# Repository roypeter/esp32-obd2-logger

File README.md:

# ESP32 OBD2 CAN Logger

A DIY OBD2 data logger built with an ESP32. Reads live engine data over CAN bus, logs to CSV (SD card or internal flash), shows live values on a small OLED display, and serves a real-time web dashboard over WiFi.

> **Note:** Only tested on a **2020 Tata Nexon 1.2L Turbo Petrol (6-speed manual)**. Should work on any car with standard OBD2 over CAN (ISO 15765-4, 500 kbps).

## Using AI to review your driving data

Download the CSV from the WiFi dashboard and upload it to an AI model like **Claude** or **Gemini Pro**. You can ask questions like:

- "How is the turbo performance?"
- "Review if all sensors are working correctly and flag any issues"
- "Is the fuel trim normal or is the engine running rich/lean?"
- "Any signs of engine problems based on this data?"

The AI can analyze thousands of rows of sensor data in seconds and give you a plain-English health report of your car.

Here's an example report generated from a real driving session:

## What it does

- Reads **30+ OBD2 PIDs**: RPM, speed, coolant temp, oil temp, MAP, IAT, engine load, timing advance, throttle, accelerator pedal, fuel trims, O2 sensors, catalyst temp, fuel rate, voltage, and more
- **Logs to CSV** at ~4 Hz with automatic session numbering — SD card preferred, falls back to ESP32 internal flash (LittleFS) if no SD card is present
- **OLED display** (optional) — rotates between live data, running averages, and session stats (max boost, trip distance, fuel economy)
- **WiFi dashboard** — connect your phone to see live gauges, download CSV files, and check PID status
- **Smart polling** — fast-changing PIDs polled at ~4 Hz, slow-changing PIDs at ~1 Hz
- **Auto-disables unsupported PIDs** — if a PID times out 10 times in a row, it stops polling it
- **Estimates current gear** from RPM/speed ratio (calibrated for Nexon 6MT gearbox)

## Parts list

| Part | Notes |
|------|-------|
| [ESP32 Dev Board](https://robocraze.com/products/esp32-development-board) | Any ESP32-WROOM-32 dev board works |
| [TJA1050 CAN Module](https://robu.in/product/tja1050-can-module-green-board/) | 5V module — needs a voltage divider on RX (see wiring). A 3.3V CAN module (e.g. SN65HVD230) is easier if you can find one |
| [Micro SD Card Module](https://robu.in/product/micro-sd-card-module/) *(optional)* | HW-125 with onboard level shifter. Power from 5V. Without it, logs to ESP32 internal flash (~1.5 MB) |
| [0.96" SSD1306 OLED Display](https://robu.in/product/0-96-oled-display-module-spi-i2c-128x64-7-pin-blue/) *(optional)* | 128x64, I2C. The logger works without it |
| [OBD2 Extension Cable](https://www.amazon.in/dp/B0F6NGFKQT) | 16-pin male to female — splice into the male end for CAN High/Low |
| SD Card *(optional)* | I use a SanDisk Ultra 64GB. Any size works — CSV files are small |
| Jumper wires, solder, etc. | -- |

I mostly order from [robocraze.com](https://robocraze.com) or [robu.in](https://robu.in) — check both for availability and pricing.

## Wiring

Full wiring details below.

### ESP32 to TJA1050 CAN Module

```
ESP32 GPIO5  ──────────────────  TJA1050 TXD
ESP32 GPIO4  ──┬── 1kΩ ────────  TJA1050 RXD     (voltage divider: 5V → 3.4V)
               └── 2.2kΩ ─────  GND
ESP32 5V     ──────────────────  TJA1050 VCC
ESP32 GND    ──────────────────  TJA1050 GND
```

> If using a 3.3V CAN transceiver (e.g. SN65HVD230), skip the voltage divider and connect RX directly.

### TJA1050 to OBD2 Connector

```
TJA1050 CANH  ──  OBD2 Pin 6  (CAN High)
TJA1050 CANL  ──  OBD2 Pin 14 (CAN Low)
TJA1050 GND     ──  OBD2 Pin 4 or 5  (Chassis/Signal Ground)
```

### ESP32 to SD Card Module (HW-125) — optional

```
ESP32 GND    ──  GND
ESP32 5V     ──  VCC
ESP32 GPIO19 ──  MISO
ESP32 GPIO23 ──  MOSI
ESP32 GPIO18 ──  SCK
ESP32 GPIO15 ──  CS
```

> If no SD card module is connected, the logger automatically falls back to the ESP32's internal flash (LittleFS, ~1.5 MB). This gives you roughly 30 minutes of logging. Download the CSV over WiFi before it fills up.

### ESP32 to OLED Display (optional)

```
ESP32 GND    ──  GND
ESP32 3.3V   ──  VCC
ESP32 GPIO21 ──  SDA
ESP32 GPIO22 ──  SCL
```

## Flashing

### Prerequisites

1. Install the [Arduino IDE](https://www.arduino.cc/en/software) (v2.x recommended)
2. Add ESP32 board support:
   - Go to **Tools → Board → Boards Manager**, search "esp32", install **esp32 by Espressif Systems**
3. Install required libraries via **Sketch → Include Library → Manage Libraries**:
   - `Adafruit SSD1306`
   - `Adafruit GFX Library`

   (SD, SPI, Wire, WiFi, and WebServer are included with the ESP32 board package.)

### Upload

1. Connect the ESP32 via USB
2. Open `main/main.ino` in Arduino IDE
3. Select your board: **Tools → Board → ESP32 Dev Module**
4. Select the correct port: **Tools → Port**
5. Click **Upload**

## Usage

### 1. Power up

Plug the ESP32 into the car's USB port (or a USB power bank for bench testing). The OBD2 extension cable connects to the car's OBD2 port under the dashboard.

On startup, the OLED (if connected) shows:
```
Nexon CAN Logger

SD  Session #1            (or "LittleFS  Session #1" if no SD card)
Total: 59000 MB
Used:  12 MB
Free:  58988 MB
```

The serial monitor (115200 baud) shows the same info plus CAN bus init status.

### 2. Connect to the WiFi dashboard

1. On your phone, connect to WiFi network: **`obd2logger`** (password: `logger@ka01`)
2. Open a browser and go to **`http://192.168.4.1`**

You'll see a live dashboard with all the gauges updating every second:

- **Dashboard** (`/`) — live gauges for all PIDs, storage bar, download/session links
- **All Sessions** (`/sessions`) — list of all logged sessions with download and delete options
- **Download Current** (`/download`) — download the active session CSV
- **Debug Log** (`/log`) — ring buffer of recent debug messages
- **PID Status** (`/timeouts`) — see which PIDs are responding and which got auto-disabled

### 3. Data logging

Logging starts automatically on boot. Each power cycle creates a new session file (`s001.csv`, `s002.csv`, ...). With an SD card, files are stored in `/data/` on the card. Without one, they go to the ESP32's internal flash (LittleFS).

CSV columns:
```
Timestamp_ms, RPM, Speed_kmh, Coolant_C, OilTemp_C, MAP_kPa, IAT_C,
Load_pct, TimingAdv_deg, Throttle_pct, AccelPedal_pct, CmdThrottle_pct,
DemandTorque_pct, ActualTorque_pct, STFT_pct, LTFT_pct, Baro_kPa,
O2S2_V, O2S2_STFT_pct, CmdEquivRatio, CatalystTemp_C, O2_SecLTFT_pct,
Gear, FuelLevel_pct, FuelRate_Lph, ModuleVoltage_V, AmbientTemp_C,
RefTorque_Nm, O2S1_Lambda, O2S1_Current_mA, AbsLoad_pct, EvapPurge_pct
```

### 4. Serial monitor output

At 115200 baud, you'll see a continuous stream like:
```
RPM:850 Spd:0 Clt:82 Oil:78 MAP:33 IAT:42 Load:18% Tmg:6.5 Thr:14% ...
```

Plus periodic status:
```
[12345] TX:482 RX:391 RX_timeout:91
[12345] TWAI state:1 txErr:0 rxErr:0 txQ:0 rxQ:0
```

## Notes

- **SD card is optional.** If no SD card is found, the logger falls back to ESP32 internal flash (LittleFS, ~1.5 MB). That's roughly 30 minutes of logging at 4 Hz — download the CSV over WiFi before it fills up. If neither SD nor LittleFS can mount, the ESP32 won't start (nothing to log to).
- **OLED is optional.** If not connected, everything else works normally.
- **Not all PIDs will work on every car.** The logger auto-disables PIDs that your car's ECU doesn't support. Check the PID Status page (`/timeouts`) to see which ones your car responds to.
- **Gear estimation** is calibrated for the Nexon 1.2T 6-speed manual gearbox. If you're using a different car, you'll need to adjust the `GEAR_RATIO_MIN[]` and `GEAR_RATIO_MAX[]` arrays in the code.
- **WiFi range** is limited to a few meters — it's meant for use inside the car.

## 3D Printable Cases

If you are looking to enclose your logger components, check out the [3D Printable Cases](3dprint/README.md) provided in the `3dprint` folder. It includes basic housings for the ESP32, S3 module, and OLED display.

## License

This project is licensed under [CC BY-NC 4.0](https://creativecommons.org/licenses/by-nc/4.0/) — free to use, share, and modify for non-commercial purposes with attribution. No warranty.

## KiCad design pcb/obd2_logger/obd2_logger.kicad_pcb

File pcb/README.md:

# PCB Carrier Board

A carrier board with sockets for all the modules. No SMD soldering — just plug in the modules and go.

Board size: **92mm x 60mm** (2-layer)

## What's on the board

| Socket | Pins | Notes |
|--------|------|-------|
| ESP32 Dev Board | 2x19 headers (38-pin) | 2.54mm pitch |
| TJA1050 CAN module | 4-pin header (5V) | With voltage divider (R1 + R2). Use this OR the SN65HVD230, not both |
| SN65HVD230 CAN module | 4-pin header (3.3V) | Direct connect, no voltage divider needed. Leave R1/R2 empty |
| HW-125 SD Card module | 6-pin header | SPI bus |
| SSD1306 OLED | 4-pin JST-XH | I2C, 3.3V |
| DS3231 RTC | 4-pin header | I2C, 3.3V (shares bus with OLED) |
| OBD2 connector | 4-pin JST-XH | CANH, CANL, GND, +12V (12V pin unused for now) |
| R1 (1kΩ) + R2 (2.2kΩ) | Through-hole | Voltage divider for TJA1050 RX. Leave empty if using SN65HVD230 |

## Generate the PCB

The PCB is generated programmatically using KiCad's `pcbnew` Python API. Run with KiCad's bundled Python:

```bash
cd pcb
/Applications/KiCad/KiCad.app/Contents/Frameworks/Python.framework/Versions/3.9/bin/python3 generate_pcb.py
```

This creates the complete PCB with components placed and traces routed at `obd2_logger/obd2_logger.kicad_pcb`.

## View in KiCad

1. Install [KiCad](https://www.kicad.org/download/) (free, open-source)
2. Open KiCad → **File → Open Project** → select `obd2_logger/obd2_logger.kicad_pro`
3. Double-click the PCB file to open in **pcbnew**
4. **View → 3D Viewer** (Alt+3) for a 3D preview
5. Export gerbers: **File → Fabrication Outputs → Gerbers**

## Order PCBs

Export gerbers from KiCad and upload to:
- [JLCPCB](https://jlcpcb.com/) — 5 boards for ~₹150, ships in ~1 week
- [PCBWay](https://www.pcbway.com/) — similar pricing

## CAN module options

The board supports two CAN transceiver modules (populate one, not both):

**Option A: TJA1050 (5V)** — Use header `J_CAN_5V`, populate R1 and R2
```
TJA1050 CRX → R1 (1kΩ) → ESP32 GPIO4
                          ↓
                     R2 (2.2kΩ) → GND
```

**Option B: SN65HVD230 (3.3V)** — Use header `J_CAN_3V3`, leave R1/R2 empty
```
SN65HVD230 RX → ESP32 GPIO4 (direct)
```

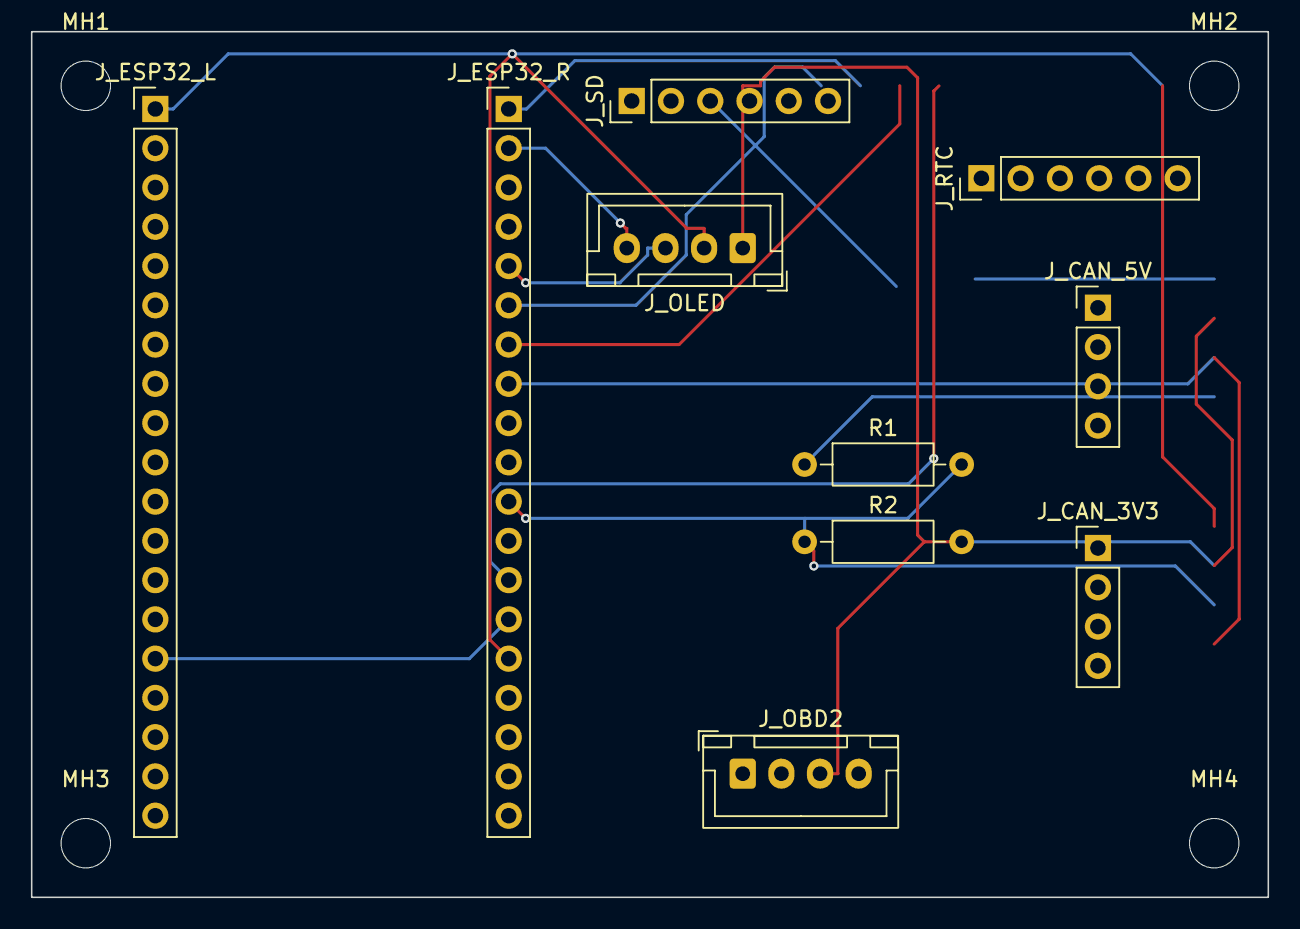
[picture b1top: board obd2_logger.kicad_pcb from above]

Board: 2 copper layers, 80.0 x 56.0 mm, 14 parts (0 on the bottom side), 12 nets.

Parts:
J_CAN_3V3: SN65HVD230; PinHeader_1x04_P2.54mm_Vertical
J_CAN_5V: TJA1050; PinHeader_1x04_P2.54mm_Vertical
J_ESP32_L: ESP32_Left; PinHeader_1x19_P2.54mm_Vertical
J_ESP32_R: ESP32_Right; PinHeader_1x19_P2.54mm_Vertical
J_OBD2: OBD2; JST_XH_B4B-XH-A_1x04_P2.50mm_Vertical
J_OLED: SSD1306_OLED; JST_XH_B4B-XH-A_1x04_P2.50mm_Vertical
J_RTC: DS3231_RTC; PinHeader_1x06_P2.54mm_Vertical
J_SD: HW-125_SD; PinHeader_1x06_P2.54mm_Vertical
MH1, MH2, MH3, MH4: MountingHole; MountingHole_3.2mm_M3
R1: 1k; R_Axial_DIN0207_L6.3mm_D2.5mm_P10.16mm_Horizontal
R2: 2.2k; R_Axial_DIN0207_L6.3mm_D2.5mm_P10.16mm_Horizontal

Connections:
CAN_RX: J_CAN_3V3.3, J_ESP32_R.11, R1.2, R2.1
CAN_RX_5V: J_CAN_5V.4, R1.1
CAN_TX: J_CAN_3V3.4, J_CAN_5V.3, J_ESP32_R.8
GND: J_CAN_3V3.2, J_CAN_5V.2, J_ESP32_L.15, J_ESP32_R.14, J_OBD2.3, J_OLED.1, J_RTC.6, J_SD.1, R2.2
I2C_SCL: J_ESP32_R.2, J_OLED.4, J_RTC.3
I2C_SDA: J_ESP32_R.5, J_OLED.3, J_RTC.4
SD_CS: J_ESP32_R.13, J_SD.6
SD_MISO: J_ESP32_R.6, J_SD.3
SD_MOSI: J_ESP32_R.1, J_SD.4
SD_SCK: J_ESP32_R.7, J_SD.5
VCC_3V3: J_CAN_3V3.1, J_ESP32_L.1, J_ESP32_R.15, J_OLED.2, J_RTC.5
VCC_5V: J_CAN_5V.1, J_ESP32_L.16, J_SD.2

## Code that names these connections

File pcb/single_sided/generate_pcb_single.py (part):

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    "JW1", "wire", ER_X + 3, jw1_y)

# JW2: CS bridge — between pins 8 and 13 to bridge CAN zone
jw2_y = esp_pin_y(10)  # between CAN_TX(8) and CAN_RX(11)
jw2 = add_fp(board, "Resistor_THT",
    "R_Axial_DIN0207_L6.3mm_D2.5mm_P10.16mm_Horizontal",
    "JW2", "wire", ER_X + 3, jw2_y)
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
# --- Direct horizontal routes (no crossings) ---

# I2C_SCL: ESP32_R pin 2 → OLED pin 4 → RTC pin 3
e_scl = pad_xy(esp_r, 2)
o_scl = pad_xy(oled, 4)
r_scl = pad_xy(rtc, 3)
tr_L(board, nets["I2C_SCL"], e_scl[0], e_scl[1], o_scl[0], o_scl[1])
tr_L(board, nets["I2C_SCL"], o_scl[0], o_scl[1], r_scl[0], r_scl[1])

# I2C_SDA: ESP32_R pin 5 → OLED pin 3 → RTC pin 4
e_sda = pad_xy(esp_r, 5)
o_sda = pad_xy(oled, 3)
r_sda = pad_xy(rtc, 4)
tr_L(board, nets["I2C_SDA"], e_sda[0], e_sda[1], o_sda[0], o_sda[1])
tr_L(board, nets["I2C_SDA"], o_sda[0], o_sda[1], r_sda[0], r_sda[1])

# SD_MISO: ESP32_R pin 6 → SD pin 3 (straight right, same Y level)
e_miso = pad_xy(esp_r, 6)
s_miso = pad_xy(sd, 3)
tr_L(board, nets["SD_MISO"], e_miso[0], e_miso[1], s_miso[0], s_miso[1])

# SD_SCK: ESP32_R pin 7 → SD pin 5 (L-shape)
e_sck = pad_xy(esp_r, 7)
s_sck = pad_xy(sd, 5)
tr_L(board, nets["SD_SCK"], e_sck[0], e_sck[1], s_sck[0], s_sck[1])

# CAN_TX: ESP32_R pin 8 → CAN_5V pin 3 → CAN_3V3 pin 4
e_ctx = pad_xy(esp_r, 8)
c5_ctx = pad_xy(can5v, 3)
c3_ctx = pad_xy(can3v, 4)
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tr(board, nets["CAN_TX"], c5_ctx[0], c5_ctx[1], c5_ctx[0], c3_ctx[1])
tr(board, nets["CAN_TX"], c5_ctx[0], c3_ctx[1], c3_ctx[0], c3_ctx[1])

# CAN_RX: ESP32_R pin 11 → R2 pin 1
e_crx = pad_xy(esp_r, 11)
r2_1 = pad_xy(r2, 1)
tr_L(board, nets["CAN_RX"], e_crx[0], e_crx[1], r2_1[0], r2_1[1])

# CAN_RX: R1 pin 2 → R2 pin 1 (voltage divider midpoint)
r1_2 = pad_xy(r1, 2)
tr_L(board, nets["CAN_RX"], r1_2[0], r1_2[1], r2_1[0], r2_1[1], h_first=False)

# CAN_RX: CAN_3V3 pin 3 → R1 pin 2
c3_crx = pad_xy(can3v, 3)
tr_L(board, nets["CAN_RX"], c3_crx[0], c3_crx[1], r1_2[0], r1_2[1])

# CAN_RX_5V: CAN_5V pin 4 → R1 pin 1
c5_crx = pad_xy(can5v, 4)
r1_1 = pad_xy(r1, 1)
tr_L(board, nets["CAN_RX_5V"], c5_crx[0], c5_crx[1], r1_1[0], r1_1[1], h_first=False)
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
# --- Jumper routes (cross other signal zones) ---

# SD_MOSI: ESP32_R pin 1 → down to JW1 pad 1 (on copper)
#          JW1 pad 1 ↔ JW1 pad 2 (wire on component side, shown on F.Cu)
#          JW1 pad 2 → right/down to SD pin 4 (on copper)
e_mosi = pad_xy(esp_r, 1)
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tr_L(board, nets["SD_MOSI"], jw1_p2[0], jw1_p2[1], s_mosi[0], s_mosi[1])


# SD_CS: ESP32_R pin 13 → up to JW2 pad 1 (on copper)
#        JW2 pad 1 ↔ JW2 pad 2 (wire on component side)
#        JW2 pad 2 → right/up to SD pin 6 (on copper)
e_cs = pad_xy(esp_r, 13)
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
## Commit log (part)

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2026-03-16 Initial commit
    ESP32 OBD2 CAN logger
2026-03-16 Use LittleFS
2026-03-17 Try pcb
2026-03-20 Improve pcb
2026-03-20 docs: add 3D print cases README and link in main README
2026-03-20 Add 3D print cases
